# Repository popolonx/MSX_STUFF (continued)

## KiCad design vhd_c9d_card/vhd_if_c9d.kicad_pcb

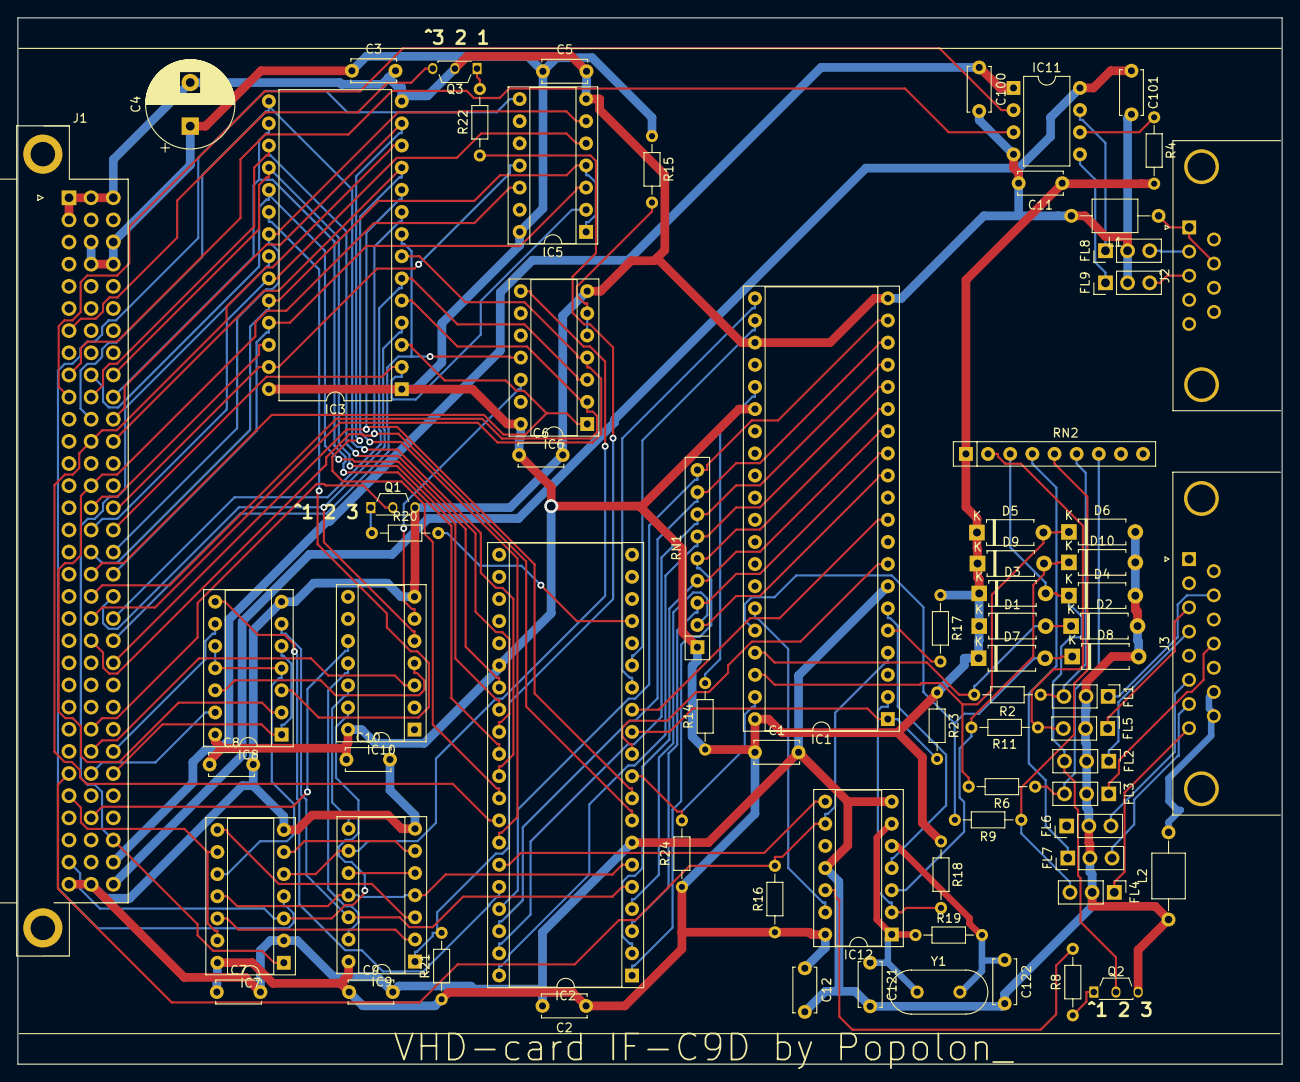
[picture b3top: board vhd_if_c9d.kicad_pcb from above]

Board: 2 copper layers, 145.0 x 120.0 mm, 74 parts (0 on the bottom side), 109 nets.

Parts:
C1, C2, C3, C5, C6, C7, C8, C9, C10, C11, C12, C100, C101: 100nF; C_Disc_D5.0mm_W2.5mm_P5.00mm
C4: 100uf/6.3V; CP_Radial_D10.0mm_P5.00mm
C121, C122: 27pF; C_Disc_D5.0mm_W2.5mm_P5.00mm
D1, D2, D3, D4, D5, D6, D7, D8, D9, D10: D; D_A-405_P7.62mm_Horizontal
FL1, FL2, FL3, FL4, FL5, FL6, FL7, FL8, FL9: EMI_Filter_LCL; PinHeader_1x03_P2.54mm_Vertical
IC1: 80C49C; DIP-40_W15.24mm_Socket
IC2: NEC D8255AC-2; DIP-40_W15.24mm_Socket
IC3: 27C256; DIP-28_W15.24mm
IC5, IC6: 74LS30; DIP-14_W7.62mm_Socket
IC7: 74LS27; DIP-14_W7.62mm_Socket
IC8: 74LS32; DIP-14_W7.62mm_Socket
IC9: 74LS02; DIP-14_W7.62mm_Socket
IC10: 74LS04; DIP-14_W7.62mm_Socket
IC11: SN751701P; DIP-8_W7.62mm
IC12: 74H004P; DIP-14_W7.62mm_Socket
J1: DIN41612_03x32_ABC; Conn_DIN41612_B096F
J2: DB9_Female; DSUB-9_Female_Horizontal_P2.77x2.84mm_EdgePinOffset7.70mm_H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
J3: DB15_Female; DSUB-15_Female_Horizontal_P2.77x2.84mm_EdgePinOffset7.70mm_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
L1, L2: L; L_Axial_L5.0mm_D3.6mm_P10.00mm_Horizontal_Murata_BL01RN1A2A2
Q1, Q2: NPN (D637); TO-92S_Wide
Q3: PNP (B641); TO-92S_Wide
R2, R6, R9, R11: 220R; R_Axial_DIN0204_L3.6mm_D1.6mm_P7.62mm_Horizontal
R4: 27K; R_Axial_DIN0204_L3.6mm_D1.6mm_P7.62mm_Horizontal
R8, R14, R15, R17, R20, R21, R23, R24: 10K; R_Axial_DIN0204_L3.6mm_D1.6mm_P7.62mm_Horizontal
R16: 47K; R_Axial_DIN0204_L3.6mm_D1.6mm_P7.62mm_Horizontal
R18: 2K2; R_Axial_DIN0204_L3.6mm_D1.6mm_P7.62mm_Horizontal
R19: 1M; R_Axial_DIN0204_L3.6mm_D1.6mm_P7.62mm_Horizontal
R22: 4K7; R_Axial_DIN0204_L3.6mm_D1.6mm_P7.62mm_Horizontal
RN1: 8x10K; R_Array_SIP9
RN2: 8x4K7; R_Array_SIP9
Y1: 6Mhz; Crystal_HC18-U_Vertical

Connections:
A1: C1.2, C2.2, C3.2, C4.2, C5.2, C6.2, C7.2, C8.2, C9.2, C10.2, C11.2, C12.2, C100.2, C101.2, C121.2, C122.2, D2.2, D4.2, D6.2, D8.2, D10.2, FL1.2, FL2.2, FL3.2, FL4.2, FL5.2, FL6.2, FL7.2, FL8.2, FL9.2, IC1.7, IC1.20, IC1.23, IC2.7, IC3.14, IC5.7, IC6.7, IC7.2, IC7.7, IC8.7, IC9.7, IC10.7, IC11.4, IC12.7, IC12.11, J1.A1, J1.A31, J1.A32, J1.B1, J1.B32, J1.C32, L1.2, L2.1, Q1.3, Q2.3, Q3.2
A2: IC7.3, IC10.13, J1.A2
A5: IC7.9, IC7.13, J1.A5
A6: IC1.4, IC12.9, J1.A6, R16.2
A23: IC11.2, J1.A23
A24: IC11.3, J1.A24
A26: J1.A26, Q3.3
B4: IC10.10, J1.B4
B6: IC8.13, J1.B6
B7: IC10.3, J1.B7
B8: J1.B8, Q1.2
B12: IC2.8, IC3.9, J1.B12
B13: IC3.7, IC6.4, J1.B13
B14: IC3.5, IC6.2, J1.B14
B15: IC3.3, IC6.1, J1.B15
B16: IC3.24, IC5.1, IC5.4, J1.B16
B17: IC3.23, IC5.5, J1.B17
B18: IC3.26, J1.B18
B19: IC5.12, IC8.2, J1.B19
B21: IC2.33, IC3.12, J1.B21
B22: IC2.31, IC3.15, J1.B22
B23: IC2.29, IC3.17, J1.B23
B24: IC2.27, IC3.19, J1.B24
B29: C1.1, C2.1, C3.1, C4.1, C5.1, C6.1, C7.1, C8.1, C9.1, C10.1, C11.1, C12.1, D1.1, D3.1, D5.1, D7.1, D9.1, IC1.26, IC1.40, IC2.26, IC3.1, IC3.28, IC5.14, IC6.14, IC7.14, IC8.14, IC9.14, IC10.14, IC12.14, J1.B29, J1.B30, J1.C29, J1.C30, R4.2, R14.1, R15.1, R16.1, R17.1, R18.1, R21.1, R23.1, R24.1, RN1.1, RN2.1
C1: C101.1, IC11.8, J1.C1
C2: C100.1, IC11.1, J1.C2
C3: IC3.22, IC7.1, J1.C3
C6: IC8.1, IC8.5, J1.C6
C7: IC8.9, J1.C7
C11: IC2.9, IC3.10, J1.C11
C12: IC3.8, IC6.11, J1.C12
C13: IC3.6, IC6.3, J1.C13
C14: IC3.4, IC10.5, J1.C14
C15: IC3.25, IC5.3, J1.C15
C16: IC3.21, IC5.6, J1.C16
C17: IC3.2, IC5.2, J1.C17
C18: IC3.27, IC5.11, J1.C18
C21: IC2.34, IC3.11, J1.C21
C22: IC2.32, IC3.13, J1.C22
C23: IC2.30, IC3.16, J1.C23
C24: IC2.28, IC3.18, J1.C24
CLK: IC1.2, IC12.2, R18.2
unnamed: C121.1, IC12.1, IC12.6, R19.1, Y1.1
unnamed: C122.1, IC12.5, R19.2, Y1.2
unnamed: D1.2, D2.1, IC1.37, R2.2
unnamed: D5.2, D6.1, IC1.38, R6.2
unnamed: D7.2, D8.1, IC1.36, R9.2
unnamed: D9.2, D10.1, IC12.3, R11.2
unnamed: FL6.3, J3.6
unnamed: FL7.3, J3.7
unnamed: FL8.3, J2.2
unnamed: FL9.3, J2.3
unnamed: IC1.5, R17.2
unnamed: IC1.6, IC12.4
unnamed: IC1.12, IC2.4, RN1.2
unnamed: IC1.13, IC2.3, RN1.3
unnamed: IC1.14, IC2.2, RN1.4
unnamed: IC1.15, IC2.1, RN1.5
unnamed: IC1.16, IC2.40, RN1.6
unnamed: IC1.17, IC2.39, RN1.7
unnamed: IC1.18, IC2.38, RN1.8
unnamed: IC1.19, IC2.37, RN1.9
unnamed: IC1.25, R14.2
unnamed: IC1.35, IC12.13
unnamed: IC2.5, IC8.6, IC9.12
unnamed: IC2.6, IC7.11, IC9.4, IC9.11
unnamed: IC2.17, R20.2
unnamed: IC2.36, IC8.8
unnamed: IC3.20, IC8.3
unnamed: IC5.8, IC7.4
unnamed: IC6.5, IC6.6, R15.2
unnamed: IC6.8, IC7.5, IC9.9
unnamed: IC7.6, IC9.6
unnamed: IC7.8, IC9.3
unnamed: IC7.10, IC8.4, IC8.10, IC8.11
unnamed: IC7.12, IC9.2
unnamed: IC9.1, R21.2, R22.1
unnamed: IC9.5, IC9.10
unnamed: IC8.12, IC10.4
unnamed: IC6.12, IC10.6
unnamed: IC9.13, IC10.11
unnamed: IC9.8, IC10.12
unnamed: IC11.6, R4.1
unnamed: IC2.35, IC12.8
unnamed: IC12.12, R8.2
unnamed: J2.1, J2.7, L1.1
unnamed: J3.14, J3.15, L2.2
unnamed: Q1.1, R20.1
unnamed: Q2.1, R8.1
unnamed: Q3.1, R22.2
P2.0_PC0: IC1.21, IC2.14
P2.1_PC1: IC1.22, IC2.15
RD_PC6: IC1.8, IC2.11
S2: FL8.1, IC11.7
S3: FL9.1, IC11.5
T0_PC5: IC1.1, IC2.12, R23.2
T1_PC7: IC1.39, IC2.10, R24.2
VHD3: FL5.1, J3.3
VHD3PULLUP: FL5.3, R11.1, RN2.2
VHD4: FL2.1, J3.4
VHD4PULLUP: D3.2, D4.1, FL2.3, Q2.2, RN2.3
VHD7: FL7.1, RN2.4
VHD8: FL4.1, J3.8
VHD8PULLUP: FL4.3, R9.1, RN2.5
VHD10: FL1.1, J3.10
VHD10PULLUP: FL1.3, R2.1, RN2.6
VHD12: FL3.1, J3.12
VHD12PULLUP: FL3.3, R6.1, RN2.7
WR_PC4: IC1.10, IC2.13

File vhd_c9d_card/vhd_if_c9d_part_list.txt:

"Source:","E:\msx\vhd_if_c9d\vhd_if_c9d.sch"
"Date:","8.6.2023 19:13:57"
"Tool:","Eeschema (5.1.5)-3"
"Component Count:","74"
"Ref","Value","Footprint","Datasheet","Manufacturer","Vendor"
"C1","100nF","Capacitor_THT:C_Disc_D5.0mm_W2.5mm_P5.00mm","","",""
"C2","100nF","Capacitor_THT:C_Disc_D5.0mm_W2.5mm_P5.00mm","","",""
"C3","100nF","Capacitor_THT:C_Disc_D5.0mm_W2.5mm_P5.00mm","","",""
"C4","100uf/6.3V","Capacitor_THT:CP_Radial_D10.0mm_P5.00mm","~","",""
"C5","100nF","Capacitor_THT:C_Disc_D5.0mm_W2.5mm_P5.00mm","","",""
"C6","100nF","Capacitor_THT:C_Disc_D5.0mm_W2.5mm_P5.00mm","","",""
"C7","100nF","Capacitor_THT:C_Disc_D5.0mm_W2.5mm_P5.00mm","","",""
"C8","100nF","Capacitor_THT:C_Disc_D5.0mm_W2.5mm_P5.00mm","","",""
"C9","100nF","Capacitor_THT:C_Disc_D5.0mm_W2.5mm_P5.00mm","","",""
"C10","100nF","Capacitor_THT:C_Disc_D5.0mm_W2.5mm_P5.00mm","","",""
"C11","100nF","Capacitor_THT:C_Disc_D5.0mm_W2.5mm_P5.00mm","","",""
"C12","100nF","Capacitor_THT:C_Disc_D5.0mm_W2.5mm_P5.00mm","","",""
"C100","100nF","Capacitor_THT:C_Disc_D5.0mm_W2.5mm_P5.00mm","","",""
"C101","100nF","Capacitor_THT:C_Disc_D5.0mm_W2.5mm_P5.00mm","","",""
"C121","27pF","Capacitor_THT:C_Disc_D5.0mm_W2.5mm_P5.00mm","","",""
"C122","27pF","Capacitor_THT:C_Disc_D5.0mm_W2.5mm_P5.00mm","","",""
"D1","1N4148","Diode_THT:D_A-405_P7.62mm_Horizontal","","",""
"D2","1N4148","Diode_THT:D_A-405_P7.62mm_Horizontal","","",""
"D3","1N4148","Diode_THT:D_A-405_P7.62mm_Horizontal","","",""
"D4","1N4148","Diode_THT:D_A-405_P7.62mm_Horizontal","","",""
"D5","1N4148","Diode_THT:D_A-405_P7.62mm_Horizontal","","",""
"D6","1N4148","Diode_THT:D_A-405_P7.62mm_Horizontal","","",""
"D7","1N4148","Diode_THT:D_A-405_P7.62mm_Horizontal","","",""
"D8","1N4148","Diode_THT:D_A-405_P7.62mm_Horizontal","","",""
"D9","1N4148","Diode_THT:D_A-405_P7.62mm_Horizontal","","",""
"D10","1N4148","Diode_THT:D_A-405_P7.62mm_Horizontal","","",""
"FL1","EMI_Filter_LCL","Connector_PinHeader_2.54mm:PinHeader_1x03_P2.54mm_Vertical","http://www.murata.com/~/media/webrenewal/support/library/cat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","",""
"FL2","EMI_Filter_LCL","Connector_PinHeader_2.54mm:PinHeader_1x03_P2.54mm_Vertical","http://www.murata.com/~/media/webrenewal/support/library/cat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","",""
"FL3","EMI_Filter_LCL","Connector_PinHeader_2.54mm:PinHeader_1x03_P2.54mm_Vertical","http://www.murata.com/~/media/webrenewal/support/library/cat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","",""
"FL4","EMI_Filter_LCL","Connector_PinHeader_2.54mm:PinHeader_1x03_P2.54mm_Vertical","http://www.murata.com/~/media/webrenewal/support/library/cat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","",""
"FL5","EMI_Filter_LCL","Connector_PinHeader_2.54mm:PinHeader_1x03_P2.54mm_Vertical","http://www.murata.com/~/media/webrenewal/support/library/cat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","",""
"FL6","EMI_Filter_LCL","Connector_PinHeader_2.54mm:PinHeader_1x03_P2.54mm_Vertical","http://www.murata.com/~/media/webrenewal/support/library/cat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","",""
"FL7","EMI_Filter_LCL","Connector_PinHeader_2.54mm:PinHeader_1x03_P2.54mm_Vertical","http://www.murata.com/~/media/webrenewal/support/library/cat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","",""
"FL8","EMI_Filter_LCL","Connector_PinHeader_2.54mm:PinHeader_1x03_P2.54mm_Vertical","http://www.murata.com/~/media/webrenewal/support/library/cat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","",""
"FL9","EMI_Filter_LCL","Connector_PinHeader_2.54mm:PinHeader_1x03_P2.54mm_Vertical","http://www.murata.com/~/media/webrenewal/support/library/cat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","",""
"IC1","80C49C","Package_DIP:DIP-40_W15.24mm_Socket","","",""
"IC2","NEC D8255AC-2","Package_DIP:DIP-40_W15.24mm_Socket","http://aturing.umcs.maine.edu/~meadow/courses/cos335/Intel82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","",""
"IC3","27C256","Package_DIP:DIP-28_W15.24mm","http://ww1.microchip.com/downloads/en/DeviceDoc/doc0014.pdf","",""
"IC5","74LS30","Package_DIP:DIP-14_W7.62mm_Socket","http://www.ti.com/lit/gpn/sn74LS30","",""
"IC6","74LS30","Package_DIP:DIP-14_W7.62mm_Socket","http://www.ti.com/lit/gpn/sn74LS30","",""
"IC7","74LS27","Package_DIP:DIP-14_W7.62mm_Socket","http://www.ti.com/lit/gpn/sn74LS27","",""
"IC8","74LS32","Package_DIP:DIP-14_W7.62mm_Socket","http://www.ti.com/lit/gpn/sn74LS32","",""
"IC9","74LS02","Package_DIP:DIP-14_W7.62mm_Socket","http://www.ti.com/lit/gpn/sn74ls02","",""
"IC10","74LS04","Package_DIP:DIP-14_W7.62mm_Socket","http://www.ti.com/lit/gpn/sn74LS04","",""
"IC11","SN751701P","Package_DIP:DIP-8_W7.62mm","http://www.ti.com/lit/ds/symlink/sn75lbc176.pdf","",""
"IC12","74H004P","Package_DIP:DIP-14_W7.62mm_Socket","https://assets.nexperia.com/documents/data-sheet/74HC_HCT04.pdf","",""
"J1","DIN41612_03x32_ABC","Connector_DIN:Conn_DIN41612_B096F","","",""
"J2","DB9_Female","Connector_Dsub:DSUB-9_Female_Horizontal_P2.77x2.84mm_EdgePinOffset7.70mm_Housed_MountingHolesOffset9.12mm"," ~","",""
"J3","DB15_Female","Connector_Dsub:DSUB-15_Female_Horizontal_P2.77x2.84mm_EdgePinOffset7.70mm_Housed_MountingHolesOffset9.12mm"," ~","",""
"L1","L","Inductor_THT:L_Axial_L5.0mm_D3.6mm_P10.00mm_Horizontal_Murata_BL01RN1A2A2","","",""
"L2","L","Inductor_THT:L_Axial_L5.0mm_D3.6mm_P10.00mm_Horizontal_Murata_BL01RN1A2A2","","",""
"Q1","NPN (D637)","Package_TO_SOT_THT:TO-92S_Wide","","",""
"Q2","NPN (D637)","Package_TO_SOT_THT:TO-92S_Wide","","",""
"Q3","PNP (B641)","Package_TO_SOT_THT:TO-92S_Wide","","",""
"R2","220R","Resistor_THT:R_Axial_DIN0204_L3.6mm_D1.6mm_P7.62mm_Horizontal","","",""
"R4","27K","Resistor_THT:R_Axial_DIN0204_L3.6mm_D1.6mm_P7.62mm_Horizontal","","",""
"R6","220R","Resistor_THT:R_Axial_DIN0204_L3.6mm_D1.6mm_P7.62mm_Horizontal","","",""
"R8","10K","Resistor_THT:R_Axial_DIN0204_L3.6mm_D1.6mm_P7.62mm_Horizontal","","",""
"R9","220R","Resistor_THT:R_Axial_DIN0204_L3.6mm_D1.6mm_P7.62mm_Horizontal","","",""
"R11","220R","Resistor_THT:R_Axial_DIN0204_L3.6mm_D1.6mm_P7.62mm_Horizontal","","",""
"R14","10K","Resistor_THT:R_Axial_DIN0204_L3.6mm_D1.6mm_P7.62mm_Horizontal","","",""
"R15","10K","Resistor_THT:R_Axial_DIN0204_L3.6mm_D1.6mm_P7.62mm_Horizontal","","",""
"R16","47K","Resistor_THT:R_Axial_DIN0204_L3.6mm_D1.6mm_P7.62mm_Horizontal","","",""
"R17","10K","Resistor_THT:R_Axial_DIN0204_L3.6mm_D1.6mm_P7.62mm_Horizontal","","",""
"R18","2K2","Resistor_THT:R_Axial_DIN0204_L3.6mm_D1.6mm_P7.62mm_Horizontal","","",""
"R19","1M","Resistor_THT:R_Axial_DIN0204_L3.6mm_D1.6mm_P7.62mm_Horizontal","","",""
"R20","10K","Resistor_THT:R_Axial_DIN0204_L3.6mm_D1.6mm_P7.62mm_Horizontal","","",""
"R21","10K","Resistor_THT:R_Axial_DIN0204_L3.6mm_D1.6mm_P7.62mm_Horizontal","","",""
"R22","4K7","Resistor_THT:R_Axial_DIN0204_L3.6mm_D1.6mm_P7.62mm_Horizontal","","",""
"R23","10K","Resistor_THT:R_Axial_DIN0204_L3.6mm_D1.6mm_P7.62mm_Horizontal","","",""
"R24","10K","Resistor_THT:R_Axial_DIN0204_L3.6mm_D1.6mm_P7.62mm_Horizontal","","",""
"RN1","8x10K","Resistor_THT:R_Array_SIP9","http://www.vishay.com/docs/31509/csc.pdf","",""
"RN2","8x4K7","Resistor_THT:R_Array_SIP9","http://www.vishay.com/docs/31509/csc.pdf","",""
"Y1","6Mhz","Crystal:Crystal_HC18-U_Vertical","~","",""

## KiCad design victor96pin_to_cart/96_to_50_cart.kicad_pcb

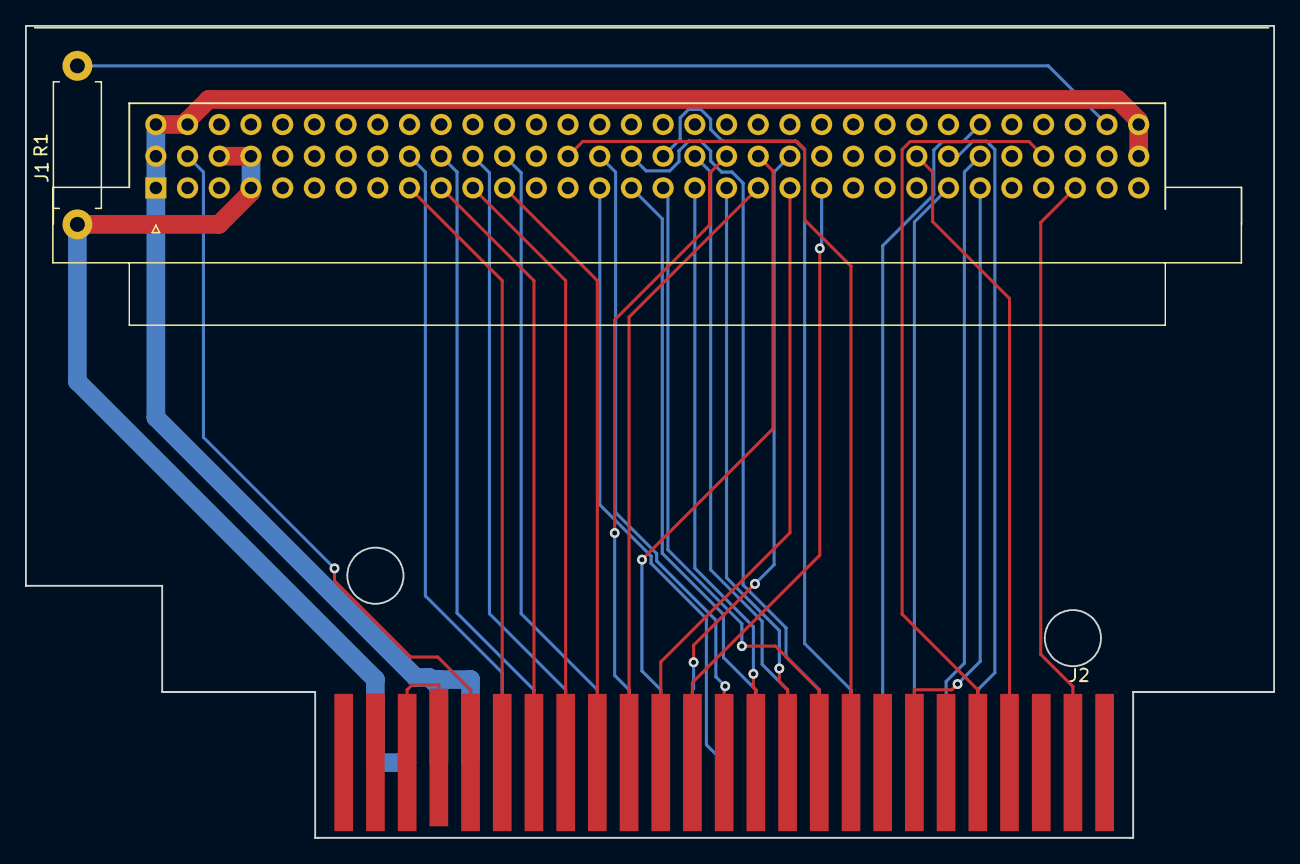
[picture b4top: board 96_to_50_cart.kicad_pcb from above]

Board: 2 copper layers, 100.0 x 65.0 mm, 3 parts (0 on the bottom side), 37 nets.

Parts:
J1: DIN41612_03x32_ABC; Conn_DIN41612_B096F_mirrored
J2: Conn_02x25_Odd_Even; msx_cartridge
R1: 4k7; R_Axial_DIN0411_L9.9mm_D3.6mm_P12.70mm_Horizontal

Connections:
5V: J1.B29, J1.B30, J1.C29, J2.45, J2.47, R1.1
A0: J1.C11, J2.28
A1: J1.B12, J2.27
A2: J1.C12, J2.30
A3: J1.B13, J2.29
A4: J1.C13, J2.32
A5: J1.B14, J2.31
A6: J1.C14, J2.22
A7: J1.B15, J2.21
A8: J1.C15, J2.24
A9: J1.B16, J2.17
A10: J1.C16, J2.20
A11: J1.B17, J2.19
A12: J1.C17, J2.23
A13: J1.B18, J2.26
A14: J1.C18, J2.25
A15: J1.B19, J2.18
BUSDIR: J1.B4, J2.10
CLK: J1.B31, J2.42
D0: J1.C21, J2.34
D1: J1.B21, J2.33
D2: J1.C22, J2.36
D3: J1.B22, J2.35
D4: J1.C23, J2.38
D5: J1.B23, J2.37
D6: J1.C24, J2.40
D7: J1.B24, J2.39
GND: J1.A1, J1.A31, J1.A32, J1.B1, J1.B32, J1.C32, J2.41, J2.43
INT01: J1.B8, J2.8
IOE: J1.B6, J2.11
JVCREQ: J1.A2, R1.2
LIR: J1.B7, J2.9
unnamed: J2.44, J2.46
RD: J1.C6, J2.14
RESET: J1.A6, J2.15
SLOT: J1.C3, J2.4
WR: J1.C7, J2.13

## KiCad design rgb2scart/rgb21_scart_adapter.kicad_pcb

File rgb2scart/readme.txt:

rgb21 to scart or din8 output and with rca input alternative

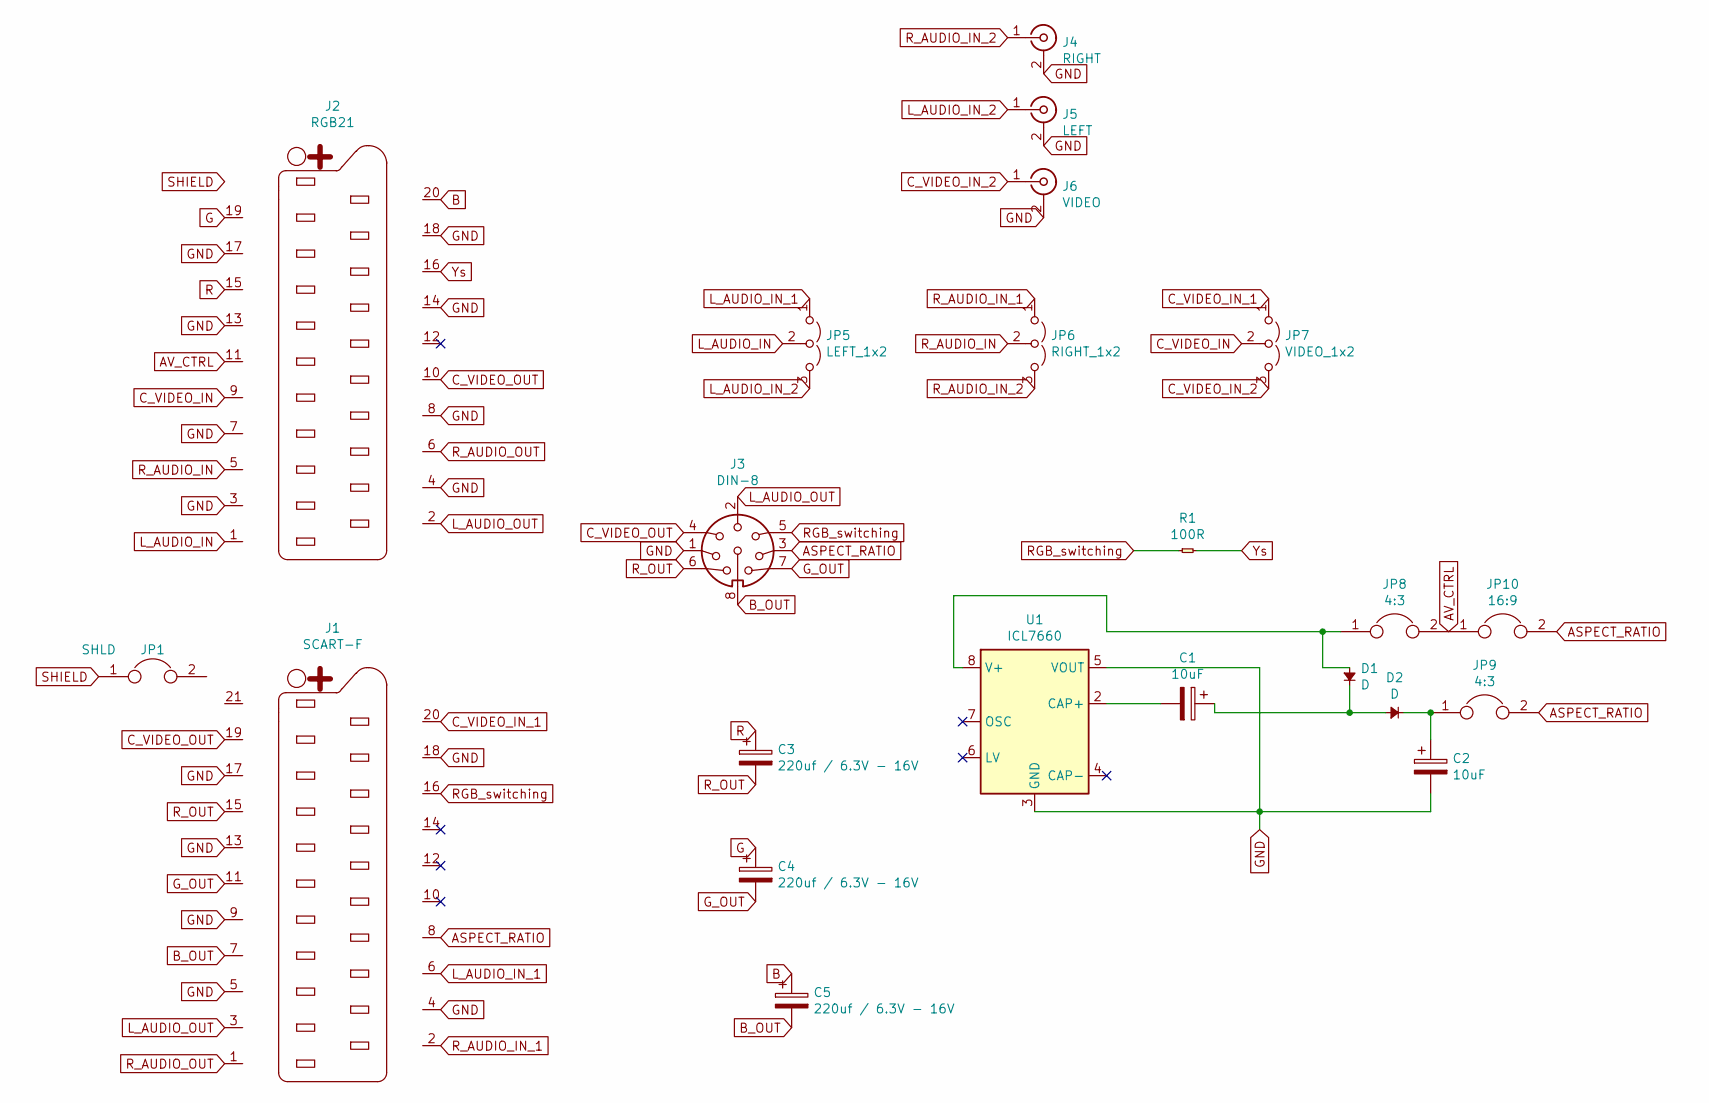
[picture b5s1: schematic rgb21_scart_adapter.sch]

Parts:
C1, C2: 10uF; CP_Radial_D8.0mm_P5.00mm
C3, C4, C5: 220uf / 6.3V - 16V; CP_Radial_D8.0mm_P5.00mm
D1, D2: D; D_A-405_P7.62mm_Horizontal
J1: SCART-F; SCART
J2: RGB21; RGB21_pcb
J3: DIN-8; din8_msx
J4: RIGHT; rca_audio
J5: LEFT; rca_audio
J6: VIDEO; rca_audio
JP1: SHLD; PinHeader_1x02_P2.54mm_Vertical
JP5: LEFT_1x2; PinHeader_1x03_P2.54mm_Vertical
JP6: RIGHT_1x2; PinHeader_1x03_P2.54mm_Vertical
JP7: VIDEO_1x2; PinHeader_1x03_P2.54mm_Vertical
JP8, JP9: 4:3; PinHeader_1x02_P2.54mm_Vertical
JP10: 16:9; PinHeader_1x02_P2.54mm_Vertical
R1: 100R; R_Axial_DIN0516_L15.5mm_D5.0mm_P7.62mm_Vertical
U1: ICL7660; DIP-8_W7.62mm_LongPads

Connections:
ASPECT_RATIO: J1.8, J3.3, JP9.2, JP10.2
AV_CTRL: J2.11, JP8.2, JP10.1
B: C5.1, J2.20
B_OUT: C5.2, J1.7, J3.8
C_VIDEO_IN: J2.9, JP7.2 (C)
C_VIDEO_IN_1: J1.20, JP7.1 (A)
C_VIDEO_IN_2: J6.1 (In), JP7.3 (B)
C_VIDEO_OUT: J1.19, J2.10, J3.4
G: C4.1, J2.19
GND: C2.2, J1.4, J1.5, J1.9, J1.13, J1.17, J1.18, J2.3, J2.4, J2.7, J2.8, J2.13, J2.14, J2.17, J2.18, J3.1, J4.2 (Ext), J5.2 (Ext), J6.2 (Ext), U1.3 (GND), U1.5 (VOUT)
G_OUT: C4.2, J1.11, J3.7
L_AUDIO_IN: J2.1, JP5.2 (C)
L_AUDIO_IN_1: J1.6, JP5.1 (A)
L_AUDIO_IN_2: J5.1 (In), JP5.3 (B)
L_AUDIO_OUT: J1.3, J2.2, J3.2
unnamed: C1.1, D1.1, D2.2
unnamed: C1.2, U1.2 (CAP+)
unnamed: C2.1, D2.1, JP9.1
unnamed: D1.2, JP8.1, U1.8 (V+)
R: C3.1, J2.15
RGB_switching: J1.16, J3.5, R1.1
R_AUDIO_IN: J2.5, JP6.2 (C)
R_AUDIO_IN_1: J1.2, JP6.1 (A)
R_AUDIO_IN_2: J4.1 (In), JP6.3 (B)
R_AUDIO_OUT: J1.1, J2.6
R_OUT: C3.2, J1.15, J3.6
Ys: J2.16, R1.2

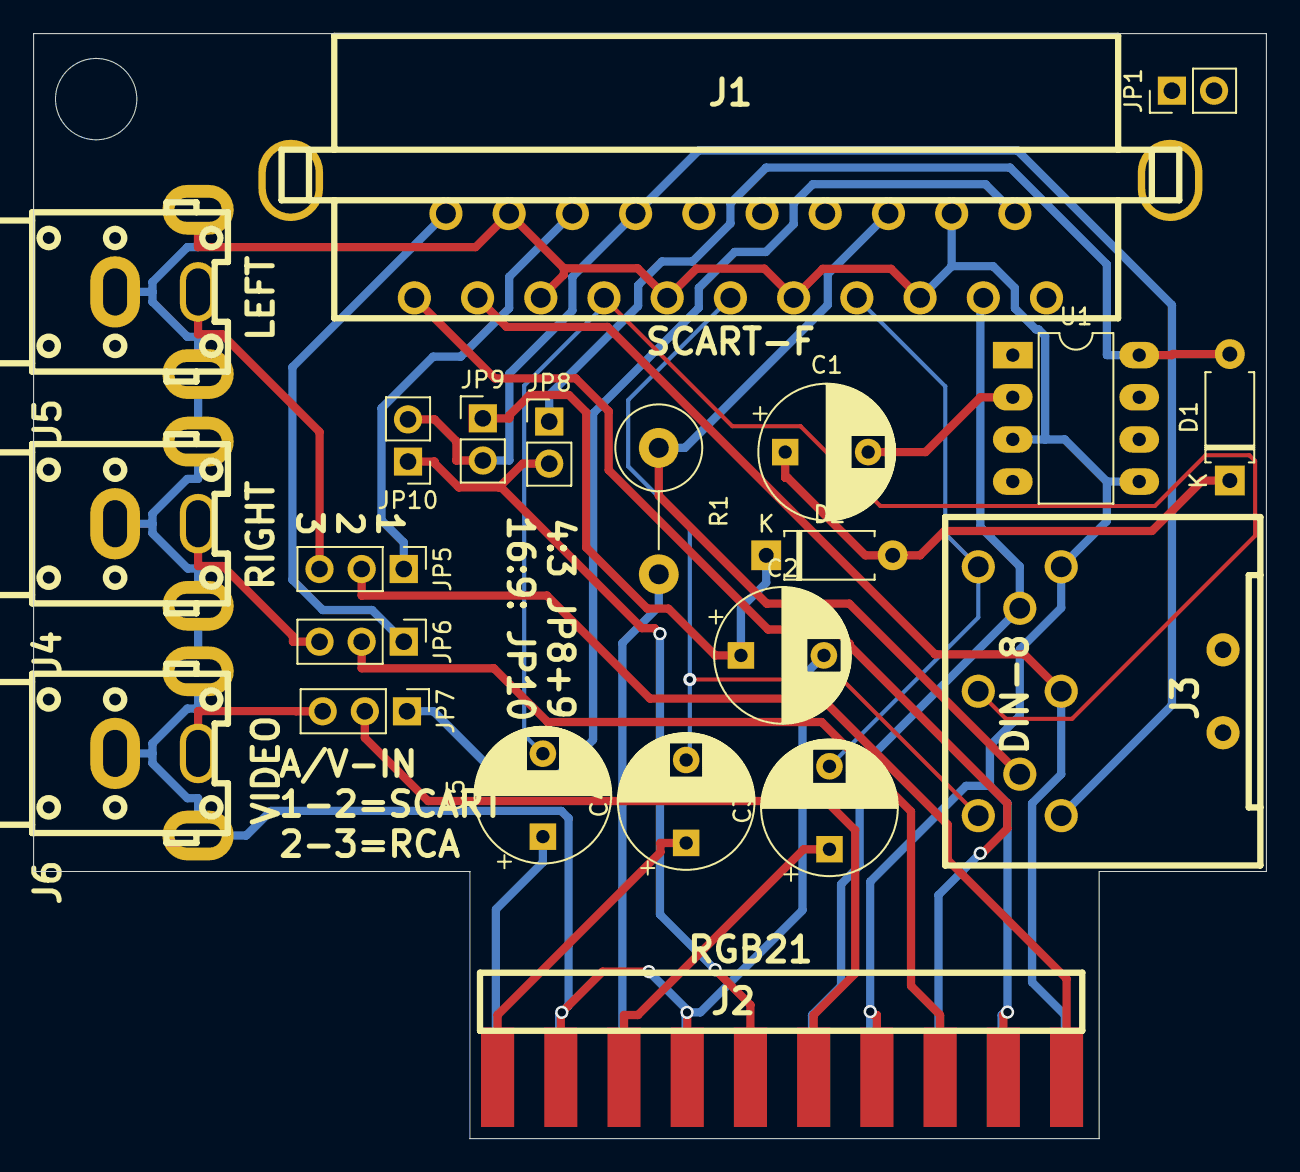
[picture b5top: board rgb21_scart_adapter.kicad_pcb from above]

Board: 2 copper layers, 74.3 x 66.6 mm, 22 parts (0 on the bottom side), 27 nets.

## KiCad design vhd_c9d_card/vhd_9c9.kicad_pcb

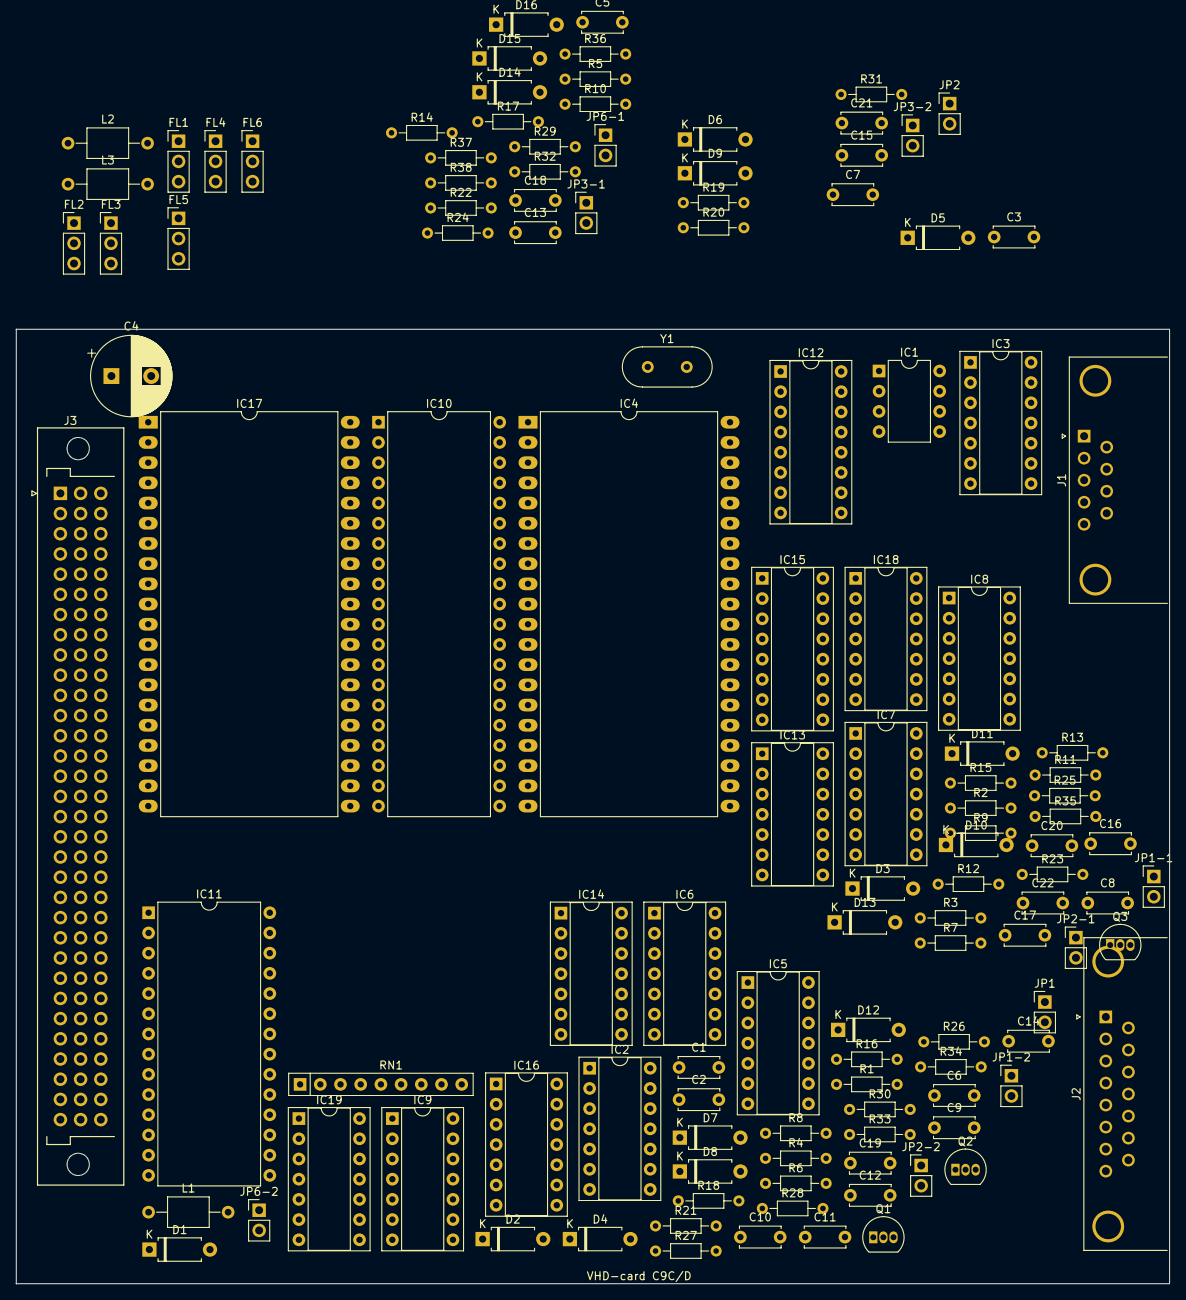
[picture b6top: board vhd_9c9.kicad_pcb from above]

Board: 2 copper layers, 145.0 x 120.0 mm, 122 parts (0 on the bottom side), 155 nets, no tracks yet.

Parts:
C1, C5, C7, C8, C10, C12, C13, C15, C16, C17, C18, C19, C20, C21, C22: 100nF; C_Disc_D5.0mm_W2.5mm_P5.00mm
C2, C3: 27pF; C_Disc_D5.0mm_W2.5mm_P5.00mm
C4: 100uf/6.3V; CP_Radial_D10.0mm_P5.00mm
C6, C9, C11, C14: ?; C_Disc_D5.0mm_W2.5mm_P5.00mm
D1, D2, D3, D4, D5, D6, D7, D8, D9, D10, D11, D12, D13, D14, D15, D16: D; D_A-405_P7.62mm_Horizontal
FL1, FL2, FL3, FL4, FL5, FL6: EMI_Filter_LCL; PinHeader_1x03_P2.54mm_Vertical
IC1: SN751701P; DIP-8_W7.62mm
IC2: 74HC04; DIP-14_W7.62mm_Socket
IC3: 74LS04; DIP-14_W7.62mm_Socket
IC4, IC17: 80C49C; DIP-40_W25.4mm_LongPads
IC5, IC6: 74LS30; DIP-14_W7.62mm_Socket
IC7: 74LS32; DIP-14_W7.62mm_Socket
IC8: 74LS27; DIP-14_W7.62mm_Socket
IC9: 74LS02; DIP-14_W7.62mm_Socket
IC10: 8255A; DIP-40_W15.24mm
IC11: 27C256; DIP-28_W15.24mm
IC12: 4538; DIP-16_W7.62mm_Socket
IC13, IC19: 4030BP; DIP-14_W7.62mm_Socket
IC14: 4069; DIP-14_W7.62mm_Socket
IC15: 4013; DIP-16_W7.62mm_Socket
IC16, IC18: 4013; DIP-14_W7.62mm_Socket
J1: DB9_Female; DSUB-9_Female_Horizontal_P2.77x2.84mm_EdgePinOffset7.70mm_H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
J2: DB15_Female; DSUB-15_Female_Horizontal_P2.77x2.84mm_EdgePinOffset4.94mm_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
J3: DIN41612_03x32_ABC; Conn_DIN41612_B096F
JP1, JP6-1, JP6-2: Jumper; PinHeader_1x02_P2.54mm_Vertical
JP1-1, JP1-2, JP2, JP2-1, JP2-2, JP3-1, JP3-2: J; PinHeader_1x02_P2.54mm_Vertical
L1, L2, L3: L; L_Axial_L5.0mm_D3.6mm_P10.00mm_Horizontal_Murata_BL01RN1A2A2
Q1, Q2: NPN (D637); TO-92_Inline
Q3: PNP (B641); TO-92_Inline
R1, R3, R5, R7, R10, R13, R22, R30: 4K7; R_Axial_DIN0204_L3.6mm_D1.6mm_P7.62mm_Horizontal
R2, R6, R9, R11, R28, R31: 220R; R_Axial_DIN0204_L3.6mm_D1.6mm_P7.62mm_Horizontal
R4, R8, R12, R14, R15, R17, R20, R21, R23, R24, R36, R37: 10K; R_Axial_DIN0204_L3.6mm_D1.6mm_P7.62mm_Horizontal
R16: 47K; R_Axial_DIN0204_L3.6mm_D1.6mm_P7.62mm_Horizontal
R18: 2K2; R_Axial_DIN0204_L3.6mm_D1.6mm_P7.62mm_Horizontal
R19: 750K; R_Axial_DIN0204_L3.6mm_D1.6mm_P7.62mm_Horizontal
R25, R27, R29, R32, R33, R34, R35, R38: ?; R_Axial_DIN0204_L3.6mm_D1.6mm_P7.62mm_Horizontal
R26: 75R ?; R_Axial_DIN0204_L3.6mm_D1.6mm_P7.62mm_Horizontal
RN1: 8x10K; R_Array_SIP9
Y1: 6Mhz; Crystal_HC18-U_Vertical

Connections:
+5V: C4.1, C5.1, C7.1, C8.1, C10.1, C12.1, C13.1, C15.1, C16.1, C17.1, C18.1, C19.1, C20.1, C21.1, C22.1, D3.1, D5.1, D7.1, D9.1, D11.1, D13.1, IC2.14, IC3.14, IC4.26, IC5.14, IC6.14, IC7.14, IC8.14, IC9.14, IC10.26, IC11.1, IC11.28, IC12.16, IC13.14, IC14.14, IC15.14, IC16.14, IC17.40, IC18.14, JP2-1.1, R1.1, R3.1, R4.2, R5.1, R7.1, R10.1, R12.1, R13.1, R14.1, R15.1, R16.1, R17.1, R18.1, R21.1, R23.1, R24.1, R25.1, R30.1, R32.1, R34.1, R36.1, R37.1, R38.1, RN1.1
-12V: C1.1, IC1.1
A2: IC3.13, IC8.3, J3.A2
A5: IC8.9, IC8.13, J3.A5
A23: J3.A23, JP6-1.1
A24: J3.A24, JP6-2.2
A26: J3.A26, Q3.2
B2: J3.B2, JP1-2.2
B4: IC3.10, J3.B4
B6: IC7.13, J3.B6
B7: IC3.3, J3.B7
B8: J3.B8, Q2.3
B12: IC10.8, IC11.9, J3.B12
B13: IC6.4, IC11.7, J3.B13
B14: IC6.2, IC11.5, J3.B14
B15: IC6.1, IC11.3, J3.B15
B16: IC5.4, IC11.24, J3.B16, JP2-2.2
B17: IC5.5, IC11.23, J3.B17
B18: IC11.26, J3.B18
B19: IC7.2, J3.B19, JP1-1.1
B21: IC10.33, IC11.12, J3.B21
B22: IC10.31, IC11.15, J3.B22
B23: IC10.29, IC11.17, J3.B23
B24: IC10.27, IC11.19, J3.B24
C3: IC8.1, IC11.22, J3.C3
C6: IC7.1, IC7.5, J3.C6
C7: IC7.9, J3.C7
C11: IC10.9, IC11.10, J3.C11
C12: IC6.11, IC11.8, J3.C12
C13: IC6.3, IC11.6, J3.C13
C14: IC3.5, IC11.4, J3.C14
C15: IC5.3, IC11.25, J3.C15
C16: IC5.6, IC11.21, J3.C16
C17: IC5.2, IC11.2, J3.C17
C18: IC11.27, J3.C18, JP3-2.2
C21: IC10.34, IC11.11, J3.C21
C22: IC10.32, IC11.13, J3.C22
C23: IC10.30, IC11.16, J3.C23
C24: IC10.28, IC11.18, J3.C24
CLK: IC2.2, IC4.2, IC17.2, R18.2
CPU2_INT_: IC12.9, IC17.6
CPU2_P1.6: IC17.33, JP2.2
CPU2_P1.7: IC15.13, IC17.34
GND: C1.2, C2.2, C3.2, C4.2, C5.2, C6.2, C7.2, C8.2, C10.2, C12.2, C13.2, C14.2, C15.2, C16.2, C17.2, C18.2, C19.2, C20.2, C21.2, C22.2, D2.2, D4.2, D6.2, D8.2, D10.2, D12.2, D14.2, FL1.2, FL2.2, FL3.2, FL4.2, FL5.2, FL6.2, IC1.4, IC2.7, IC3.7, IC4.7, IC4.20, IC5.7, IC6.7, IC7.7, IC8.2, IC8.7, IC9.7, IC10.7, IC11.14, IC12.1, IC12.8, IC12.15, IC13.7, IC14.7, IC15.4, IC15.6, IC15.7, IC15.8, IC15.10, IC16.4, IC16.6, IC16.7, IC16.8, IC16.10, IC17.7, IC17.12, IC17.13, IC17.14, IC17.15, IC17.16, IC17.17, IC17.18, IC17.19, IC17.20, IC18.4, IC18.6, IC18.7, IC18.8, IC18.10, IC19.2, J1.1, J1.7, JP1.1, L1.1, Q1.2, Q2.2, Q3.3, R26.2
unnamed: C2.1, IC2.1, IC2.6, R19.1, Y1.1
unnamed: C3.1, IC2.5, R19.2, Y1.2
unnamed: C6.1, IC12.2, R25.2
unnamed: C9.2, R27.1
unnamed: C11.1, IC14.5, R27.2, R29.1
unnamed: C11.2, IC14.6, R29.2, R33.1
unnamed: C14.1, IC12.14, R34.2
unnamed: D1.2, D2.1, IC4.37, R2.2
unnamed: D3.2, D4.1, FL2.3, Q1.3, R3.2
unnamed: D5.2, D6.1, IC4.38, R6.2
unnamed: D7.2, D8.1, IC4.36, R9.2
unnamed: D9.2, D10.1, IC2.3, R11.2
unnamed: D11.2, D12.1, IC14.3, R28.2
unnamed: D13.2, D14.1, IC14.1, R31.2
unnamed: D15.1, IC18.1
unnamed: D15.2, D16.2, IC15.9, R38.2
unnamed: D16.1, IC18.13
unnamed: FL1.3, R1.2, R2.1
unnamed: FL3.3, R5.2, R6.1
unnamed: FL4.3, R7.2, R9.1
unnamed: FL5.3, R11.1
unnamed: IC1.2, JP6-1.2
unnamed: IC1.3, JP6-2.1
unnamed: IC1.6, R4.1
unnamed: IC2.4, IC4.6
unnamed: IC2.12, R8.2
unnamed: IC2.13, IC4.35
unnamed: IC3.4, IC7.12
unnamed: IC3.6, IC6.12
unnamed: IC3.11, IC9.13
unnamed: IC3.12, IC9.8
unnamed: IC4.5, R17.2
unnamed: IC4.25, R14.2
unnamed: IC5.1, JP2-1.2, JP2-2.1
unnamed: IC5.8, IC8.4
unnamed: IC5.11, JP3-1.2, JP3-2.1
unnamed: IC5.12, JP1-1.2, JP1-2.1
unnamed: IC6.5, IC6.6, R15.2
unnamed: IC6.8, IC8.5, IC9.9
unnamed: IC7.4, IC7.10, IC7.11, IC8.10
unnamed: IC8.6, IC9.6
unnamed: IC8.8, IC9.3
unnamed: IC8.12, IC9.2
unnamed: IC9.1, R21.2, R22.1
unnamed: IC9.5, IC9.10
unnamed: IC4.15, IC10.1, RN1.5
unnamed: IC4.14, IC10.2, RN1.4
unnamed: IC4.13, IC10.3, RN1.3
unnamed: IC4.12, IC10.4, RN1.2
unnamed: IC7.6, IC9.12, IC10.5
unnamed: IC8.11, IC9.4, IC9.11, IC10.6
unnamed: IC10.17, R20.2
unnamed: IC2.8, IC10.35
unnamed: IC7.8, IC10.36
unnamed: IC4.19, IC10.37, RN1.9
unnamed: IC4.18, IC10.38, RN1.8
unnamed: IC4.17, IC10.39, RN1.7
unnamed: IC4.16, IC10.40, RN1.6
unnamed: IC7.3, IC11.20
unnamed: IC12.5, IC12.7, IC15.3
unnamed: IC12.3, IC12.11, IC12.13, R32.2
unnamed: IC12.12, IC15.1, IC15.11, IC16.3, IC18.11
unnamed: IC14.4, IC17.1
unnamed: IC14.9, R33.2, R35.1
unnamed: IC14.10, IC16.5, IC16.9, IC19.5, IC19.9, R35.2
unnamed: IC14.8, IC14.11
unnamed: IC14.12, IC17.39
unnamed: IC15.2, IC15.5, IC16.11, IC18.3
unnamed: IC16.1, IC19.6
unnamed: IC16.13, IC19.8
unnamed: IC17.5, R37.2
unnamed: IC17.25, R36.2
unnamed: IC18.5, IC19.4
unnamed: IC18.9, IC19.10
unnamed: IC19.12, IC19.13
unnamed: J2.6, L3.1
unnamed: J2.7, L2.1
unnamed: J2.14, J2.15, L1.2
unnamed: JP3-1.1, R12.2
unnamed: Q1.1, R8.1
unnamed: Q2.1, R20.1
unnamed: Q3.1, R22.2
unnamed: R30.2, R31.1
P1.0_CPU2_P2.0: IC4.27, IC17.21
P1.1_CPU2_P2.1: IC4.28, IC17.22
P1.2_CPU2_P2.2: IC4.29, IC17.23
P1.3_CPU2_P2.3: IC4.30, IC17.24
P1.4_CPU2_P2.4: IC4.31, IC17.35
P1.5_CPU2_P2.5: IC4.32, IC17.36
P1.6_CPU2_P2.6: IC4.33, IC17.37
P1.7_CPU2_P2.7: IC4.34, IC17.38
P2.0_PC0: IC4.21, IC10.14
P2.1_PC1: IC4.22, IC10.15, JP2.1
P2.2_CPU2_P1.5: IC4.23, IC17.32, JP1.2
P2.3_CPU2_P1.4: IC4.24, IC17.31
RD_PC6: IC4.8, IC10.11
RESET_: IC2.9, IC4.4, IC17.4, R16.2
S2: IC1.7, J1.2
S3: IC1.5, J1.3
T0_PC5: IC4.1, IC10.12, R23.2
T1_PC7: IC4.39, IC10.10, R24.2
VHD3: FL5.1, J2.3
VHD4: FL2.1, J2.4
VHD6: C9.1, L3.2, R26.1
VHD7: L2.2, R13.2, R28.1
VHD8: FL4.1, J2.8
VHD9: FL6.1, J2.9
VHD9_INV: IC12.4, IC14.2, IC14.13
VHD10: FL1.1, J2.10
VHD12: FL3.1, J2.12
WR_PC4: IC4.10, IC10.13

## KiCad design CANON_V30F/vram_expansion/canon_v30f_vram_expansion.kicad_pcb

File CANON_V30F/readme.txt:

canon V30F stuff
-rom dumps
-kicad files for VRAM expansion board (NOTE! experimental version)

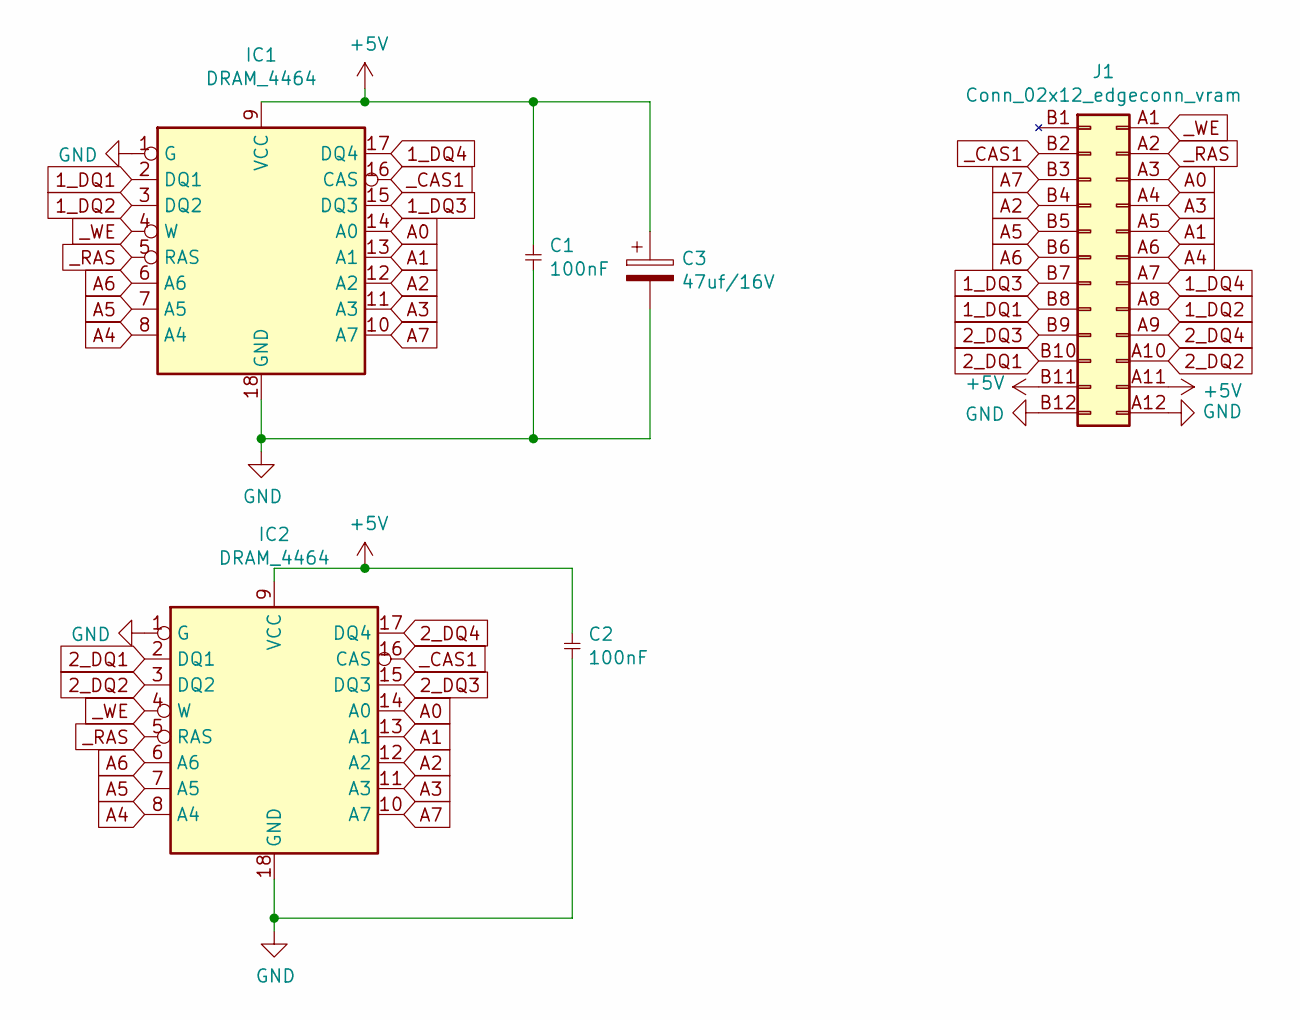
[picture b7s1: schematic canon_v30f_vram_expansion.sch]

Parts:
C1, C2: 100nF; C_Disc_D4.7mm_W2.5mm_P5.00mm
C3: 47uf/16V; CP_Radial_D8.0mm_P5.00mm
IC1, IC2: DRAM_4464; DIP-18_W7.62mm
J1: Conn_02x12_edgeconn_vram; msx_vram_expansion

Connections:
1_DQ1: IC1.2 (DQ1), J1.B8 (Pin_5)
1_DQ2: IC1.3 (DQ2), J1.A8 (Pin_20)
1_DQ3: IC1.15 (DQ3), J1.B7 (Pin_6)
1_DQ4: IC1.17 (DQ4), J1.A7 (Pin_19)
2_DQ1: IC2.2 (DQ1), J1.B10 (Pin_3)
2_DQ2: IC2.3 (DQ2), J1.A10 (Pin_22)
2_DQ3: IC2.15 (DQ3), J1.B9 (Pin_4)
2_DQ4: IC2.17 (DQ4), J1.A9 (Pin_21)
+5V: C1.1, C2.1, C3.1, IC1.9 (VCC), IC2.9 (VCC), J1.A11 (Pin_23), J1.B11 (Pin_2)
A0: IC1.14 (A0), IC2.14 (A0), J1.A3 (Pin_15)
A1: IC1.13 (A1), IC2.13 (A1), J1.A5 (Pin_17)
A2: IC1.12 (A2), IC2.12 (A2), J1.B4 (Pin_9)
A3: IC1.11 (A3), IC2.11 (A3), J1.A4 (Pin_16)
A4: IC1.8 (A4), IC2.8 (A4), J1.A6 (Pin_18)
A5: IC1.7 (A5), IC2.7 (A5), J1.B5 (Pin_8)
A6: IC1.6 (A6), IC2.6 (A6), J1.B6 (Pin_7)
A7: IC1.10 (A7), IC2.10 (A7), J1.B3 (Pin_10)
GND: C1.2, C2.2, C3.2, IC1.1 (G), IC1.18 (GND), IC2.1 (G), IC2.18 (GND), J1.A12 (Pin_24), J1.B12 (Pin_1)
_CAS1: IC1.16 (CAS), IC2.16 (CAS), J1.B2 (Pin_11)
_RAS: IC1.5 (RAS), IC2.5 (RAS), J1.A2 (Pin_14)
_WE: IC1.4 (W), IC2.4 (W), J1.A1 (Pin_13)
